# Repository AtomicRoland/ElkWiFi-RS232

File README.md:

# ElkWiFi-RS232
A small add on board to provide a real RS232 interface for the Electron and BBC Micro WiFi board

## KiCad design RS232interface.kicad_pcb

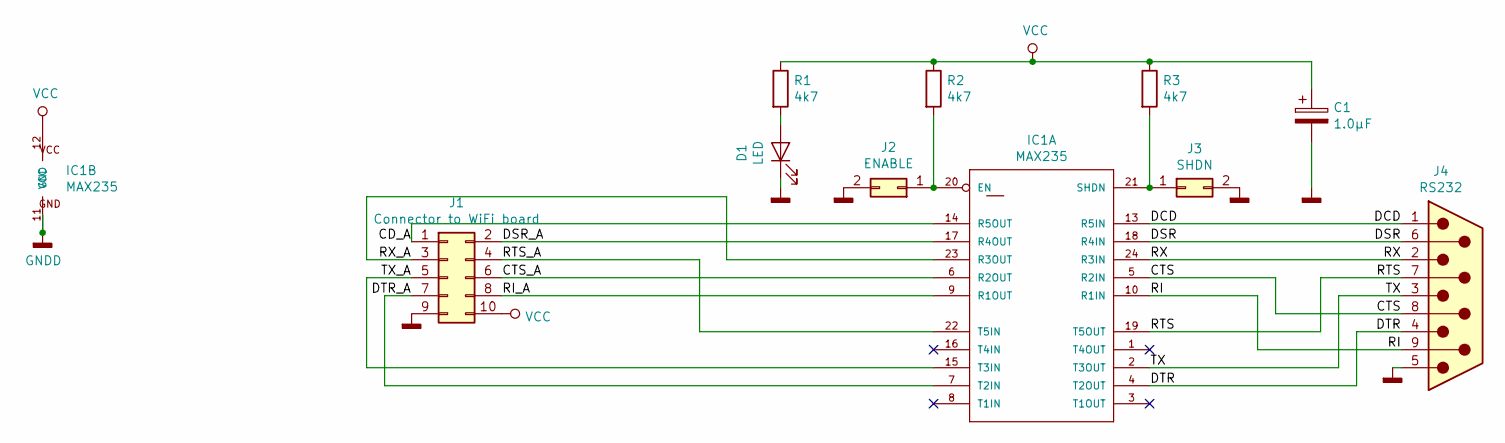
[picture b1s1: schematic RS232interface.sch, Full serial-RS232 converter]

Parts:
C1: 1.0µF; CP_Radial_D5.0mm_P2.50mm
D1: LED; LED_D3.0mm
IC1: MAX235; DIP-24_W15.24mm_Socket_LongPads
J1: Connector to WiFi board; PinHeader_2x05_P2.54mm_Vertical
J2: ENABLE; PinHeader_1x02_P2.54mm_Vertical
J3: SHDN; PinHeader_1x02_P2.54mm_Vertical
J4: RS232; DSUB-9_Male_Horizontal_P2.77x2.84mm_EdgePinOffset14.56mm_Ho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
R1, R2, R3: 4k7; R_Axial_DIN0411_L9.9mm_D3.6mm_P15.24mm_Horizontal

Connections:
/CD_A: IC1.14 (R5OUT), J1.1
/CTS: IC1.5 (R2IN), J4.8
/CTS_A: IC1.6 (R2OUT), J1.6
/DCD: IC1.13 (R5IN), J4.1
/DSR: IC1.18 (R4IN), J4.6
/DSR_A: IC1.17 (R4OUT), J1.2
/DTR: IC1.4 (T2OUT), J4.4
/DTR_A: IC1.7 (T2IN), J1.7
/RI: IC1.10 (R1IN), J4.9
/RI_A: IC1.9 (R1OUT), J1.8
/RTS: IC1.19 (T5OUT), J4.7
/RTS_A: IC1.22 (T5IN), J1.4
/RX: IC1.24 (R3IN), J4.2
/RX_A: IC1.23 (R3OUT), J1.3
/TX: IC1.2 (T3OUT), J4.3
/TX_A: IC1.15 (T3IN), J1.5
GNDD: C1.2, D1.1 (K), IC1.11 (GND), J1.9, J2.2, J3.2, J4.5
unnamed: D1.2 (A), R1.2
unnamed: IC1.20 (EN), J2.1, R2.2
unnamed: IC1.21 (SHDN), J3.1, R3.2
VCC: C1.1, IC1.12 (VCC), J1.10, R1.1, R2.1, R3.1

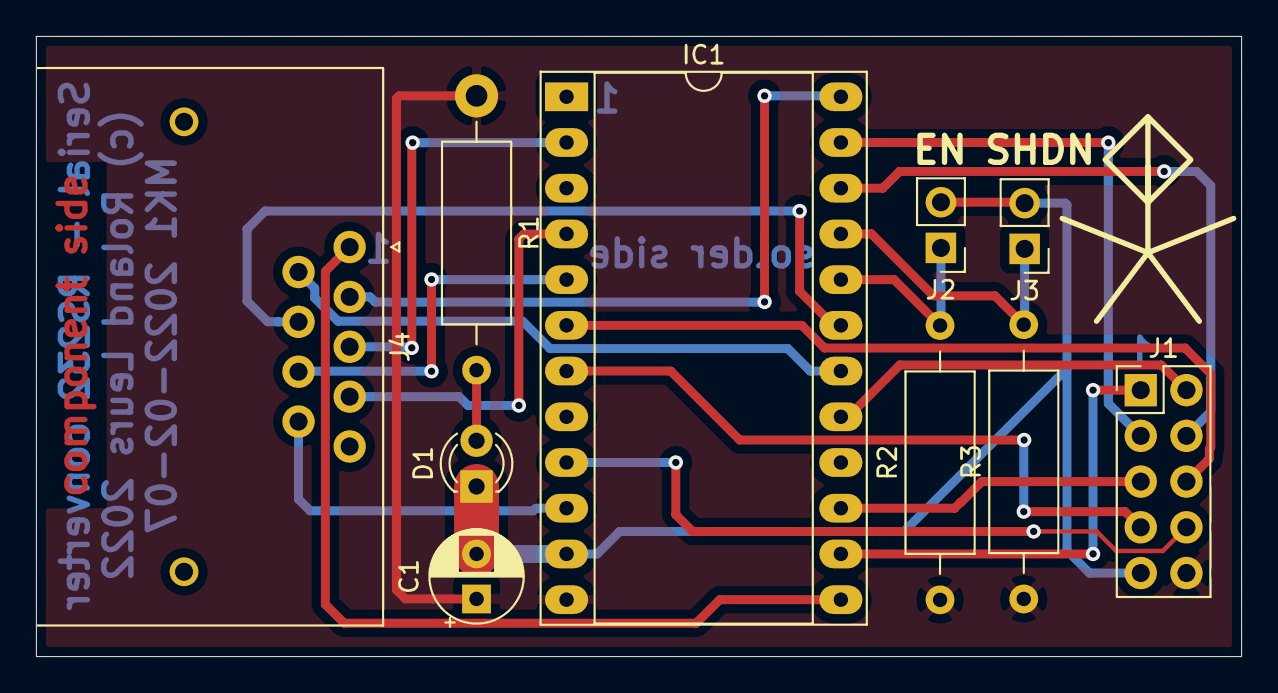
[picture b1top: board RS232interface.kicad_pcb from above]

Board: 2 copper layers, 67.0 x 34.5 mm, 10 parts (0 on the bottom side), 21 nets.

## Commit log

2022-07-24 Add files via upload
    These are the KiCad design files. In the "production" folder you'll find the Gerber files you need to have the boards produced.
